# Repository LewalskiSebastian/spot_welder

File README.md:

# spot_welder
Spot welder controller with adjustable transformator working time

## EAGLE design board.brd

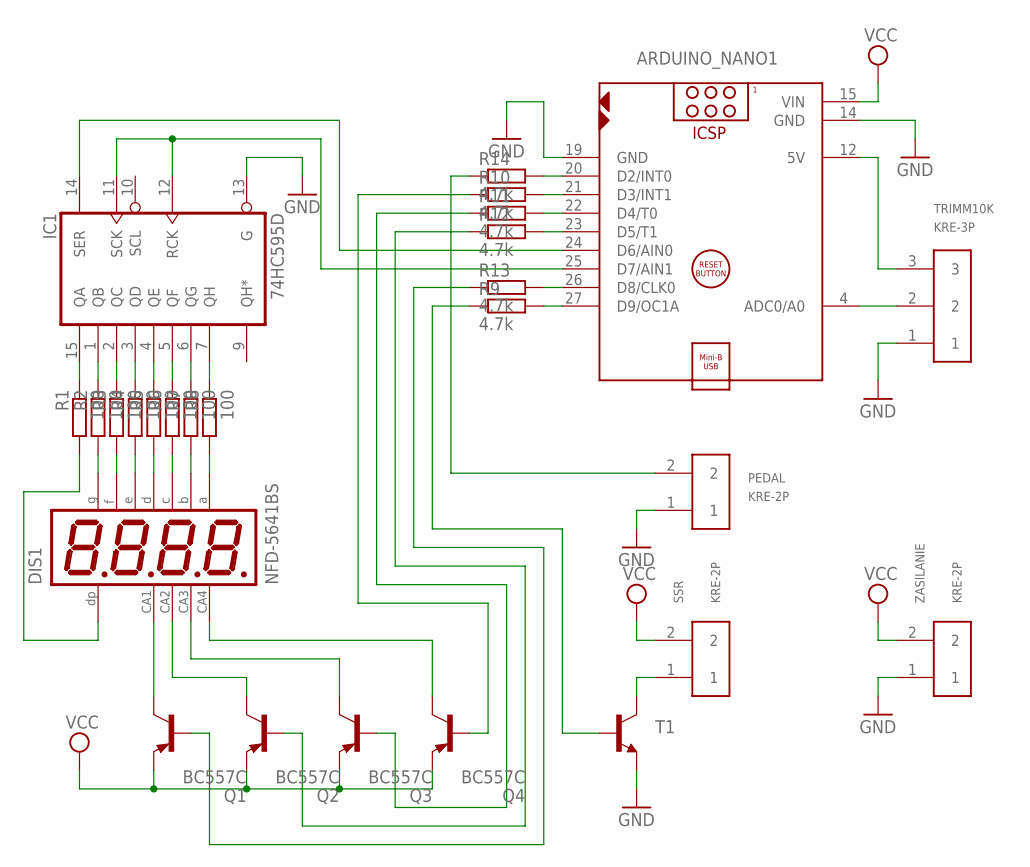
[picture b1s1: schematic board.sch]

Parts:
ARDUINO_NANO1: ARDUINO_NANO
DIS1: NFD-5641BS; NFD-5641
IC1: 74HC595D; SO16
PEDAL: KRE-2P
Q1, Q2, Q3, Q4: BC557C; TO92-EBC
R1, R2, R3, R4, R5, R6, R7, R8: 100; 0207/10
R9, R10, R11, R12, R13, R14: 4.7k; 0207/10
SSR: KRE-2P
T1: BC337-NPN-TO92-CBE; TO92-CBE
TRIMM10K: KRE-3P
ZASILANIE: KRE-2P

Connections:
GND: ARDUINO_NANO1.14 (GND), ARDUINO_NANO1.19 (GND), IC1.8 (GND), IC1.13 (G), PEDAL.1, T1.E, TRIMM10K.1, ZASILANIE.1
unnamed: IC1.15 (QA), R1.1
unnamed: IC1.1 (QB), R2.1
unnamed: IC1.2 (QC), R3.1
unnamed: IC1.3 (QD), R4.1
unnamed: IC1.4 (QE), R5.1
unnamed: IC1.5 (QF), R6.1
unnamed: IC1.6 (QG), R7.1
unnamed: IC1.7 (QH), R8.1
unnamed: DIS1.P$5, R2.2
unnamed: DIS1.P$10, R3.2
unnamed: DIS1.P$1, R4.2
unnamed: DIS1.P$2, R5.2
unnamed: DIS1.P$4, R6.2
unnamed: DIS1.P$7, R7.2
unnamed: DIS1.P$11, R8.2
unnamed: DIS1.P$3, R1.2
unnamed: DIS1.P$12, Q1.C
unnamed: DIS1.P$9, Q2.C
unnamed: DIS1.P$8, Q3.C
unnamed: DIS1.P$6, Q4.C
unnamed: ARDUINO_NANO1.26 (D8/CLK0), R13.2
unnamed: ARDUINO_NANO1.23 (D5/T1), R12.2
unnamed: ARDUINO_NANO1.22 (D4/T0), R11.2
unnamed: ARDUINO_NANO1.21 (D3/INT1), R10.2
unnamed: Q4.B, R10.1
unnamed: ARDUINO_NANO1.20 (D2/INT0), R14.2
unnamed: Q3.B, R11.1
unnamed: R9.1, T1.B
unnamed: Q2.B, R12.1
unnamed: Q1.B, R13.1
unnamed: ARDUINO_NANO1.24 (D6/AIN0), IC1.14 (SER)
unnamed: ARDUINO_NANO1.25 (D7/AIN1), IC1.11 (SCK), IC1.12 (RCK)
unnamed: SSR.1, T1.C
unnamed: ARDUINO_NANO1.27 (D9/OC1A), R9.2
unnamed: ARDUINO_NANO1.12 (5V), TRIMM10K.3
unnamed: PEDAL.2, R14.1
unnamed: ARDUINO_NANO1.4 (ADC0/A0), TRIMM10K.2
VCC: ARDUINO_NANO1.15 (VIN), IC1.16 (VCC), Q1.E, Q2.E, Q3.E, Q4.E, SSR.2, ZASILANIE.2

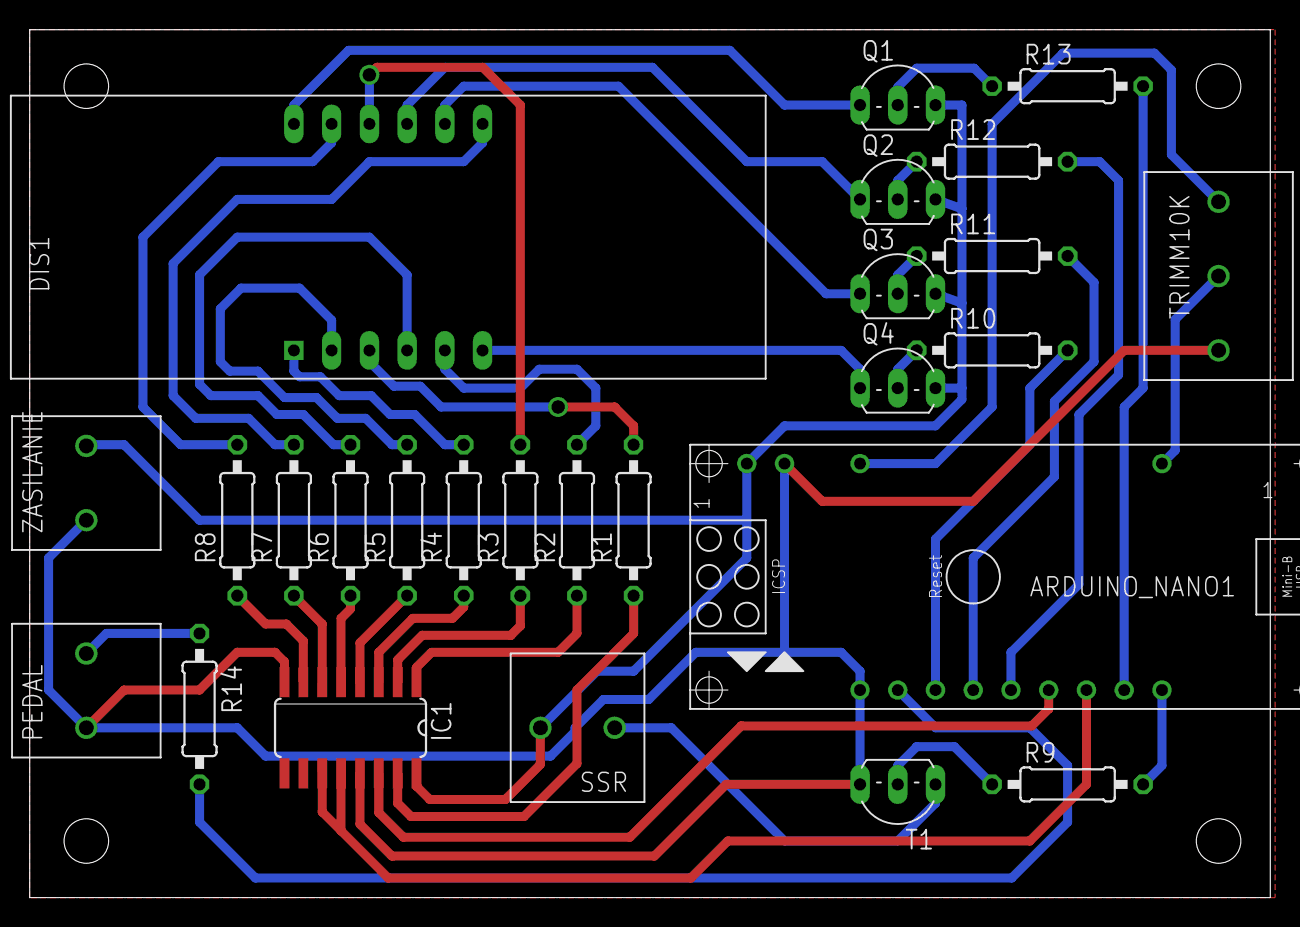
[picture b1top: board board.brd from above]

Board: 2 copper layers, 83.5 x 58.4 mm, 26 parts (0 on the bottom side), 39 nets.

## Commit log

2020-09-21 Add Arduino files
2020-09-27 Add Eagle board files
2021-01-12 Potentiometre replaced with encoder
    Add encoder handling and saving milis value to eeprom on power off
